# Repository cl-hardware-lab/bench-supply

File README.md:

# bench-supply
Bench power supply PCB

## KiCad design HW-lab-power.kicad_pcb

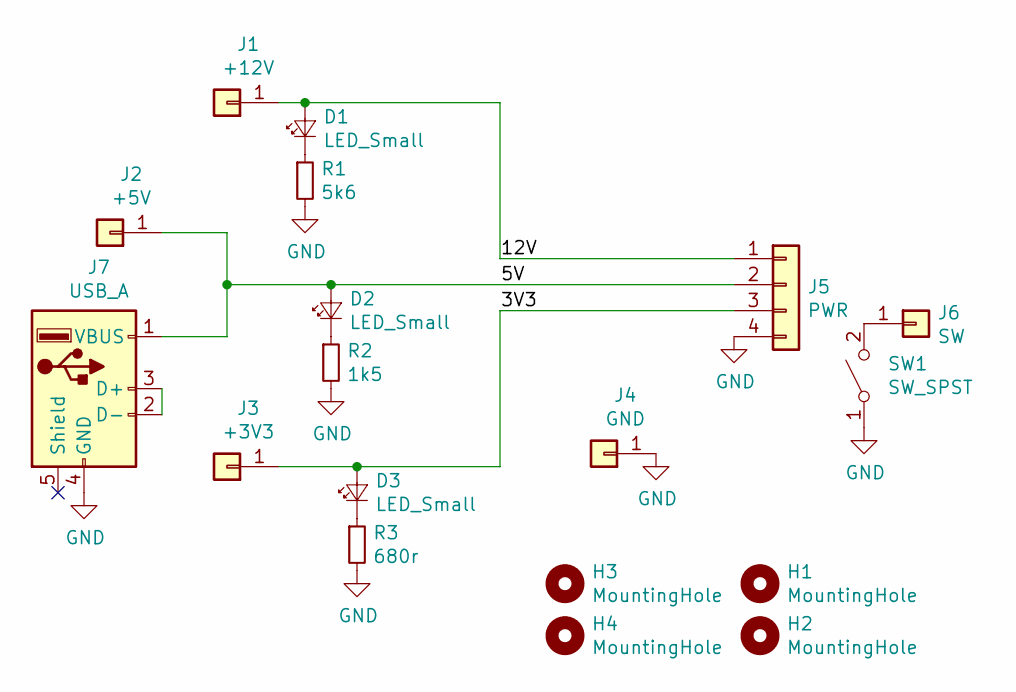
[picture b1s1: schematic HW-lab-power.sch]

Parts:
D1, D2, D3: LED_Small; LED_0805_2012Metric
H1, H2: MountingHole; MountingHole_3.7mm
H3, H4: MountingHole; MountingHole_3.2mm_M3
J1: +12V; 552-0100; Farnell 2112491
J2: +5V; 552-0100; Farnell 2112491
J3: +3V3; 552-0100; Farnell 2112491
J4: GND; 552-0100; Farnell 2112490
J5: PWR; SolderWirePad_1x04_P7.62mm_Drill2.5mm
J6: SW; SolderWirePad_1x01_Drill1.5mm
J7: USB_A; USB_A_Molex_105057_Vertical; Farnell 1758742
R1: 5k6; R_0603_1608Metric
R2: 1k5; R_0603_1608Metric
R3: 680r; R_0603_1608Metric
SW1: SW_SPST; DIP-6_226_ELL

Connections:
/3V3: D3.2 (A), J3.1, J5.3
/5V: D2.2 (A), J2.1, J5.2, J7.1 (VBUS)
/12V: D1.2 (A), J1.1, J5.1
GND: J4.1, J5.4, J7.4 (GND), R1.2, R2.2, R3.2, SW1.1 (A)
unnamed: D1.1 (K), R1.1
unnamed: D2.1 (K), R2.1
unnamed: D3.1 (K), R3.1
unnamed: J6.1, SW1.2 (B)
unnamed: J7.2 (D-), J7.3 (D+)

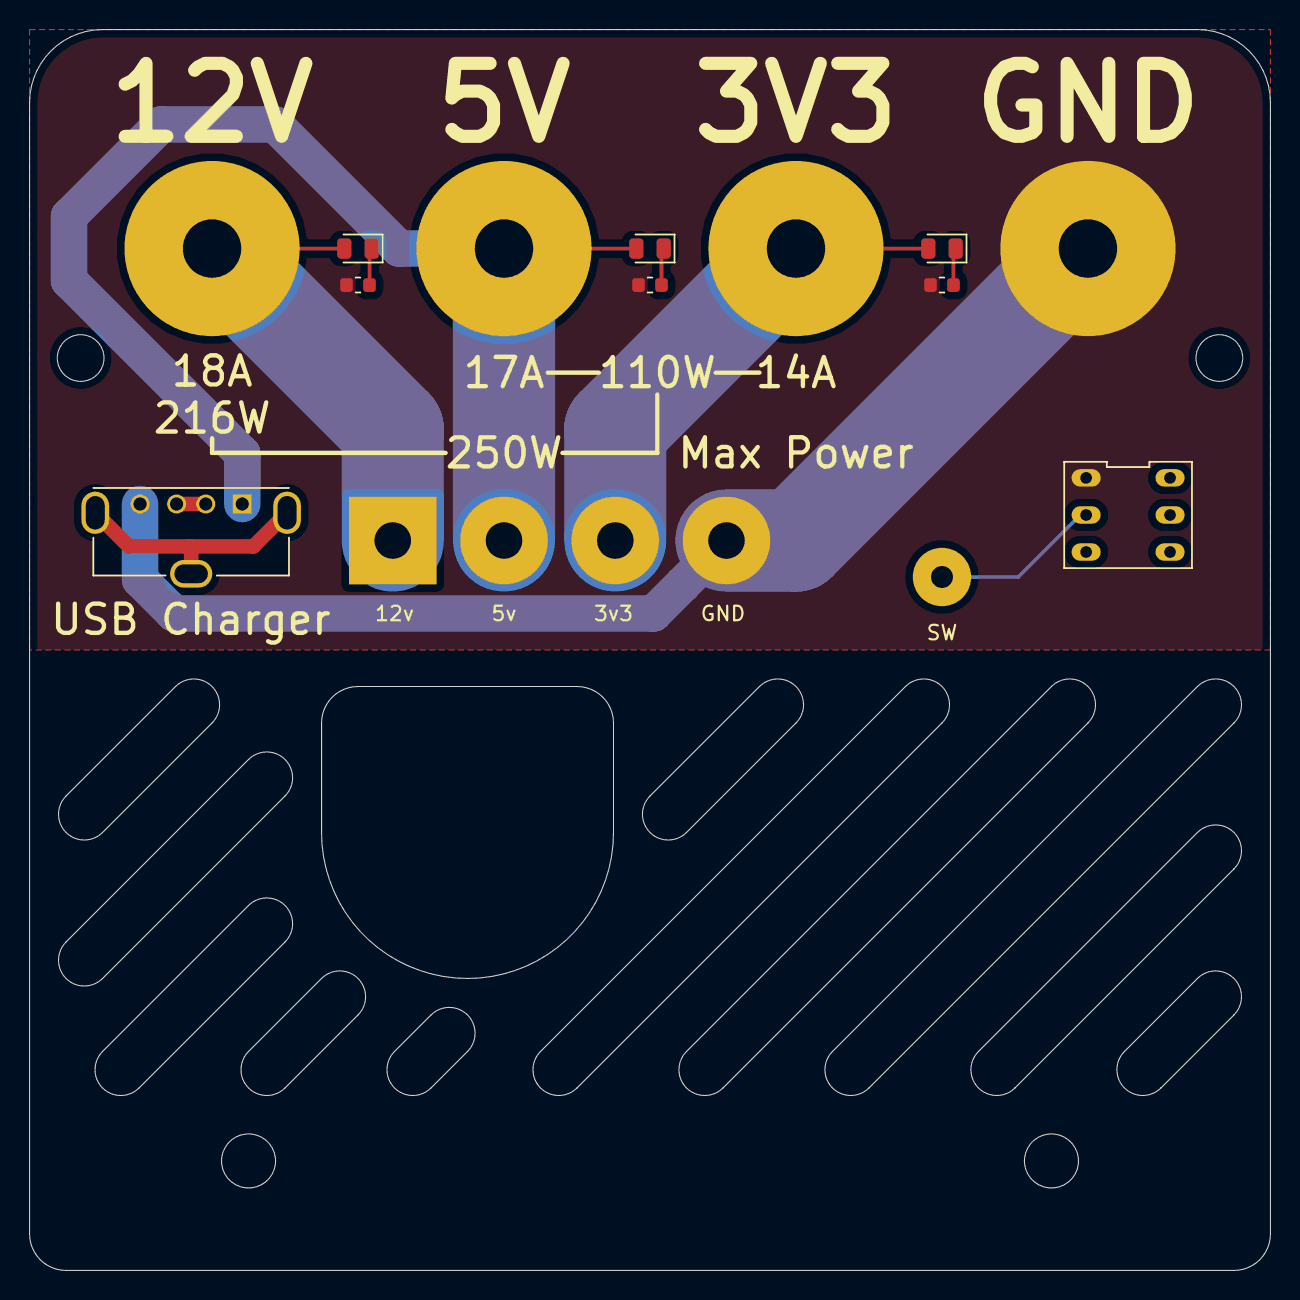
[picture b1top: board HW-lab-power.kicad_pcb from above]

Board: 2 copper layers, 85.0 x 85.0 mm, 18 parts (0 on the bottom side), 9 nets.

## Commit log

2020-01-17 Initial board setup
2020-01-23 Finished tweaks and setup for first revision
2020-02-10 Revision 1 final files
